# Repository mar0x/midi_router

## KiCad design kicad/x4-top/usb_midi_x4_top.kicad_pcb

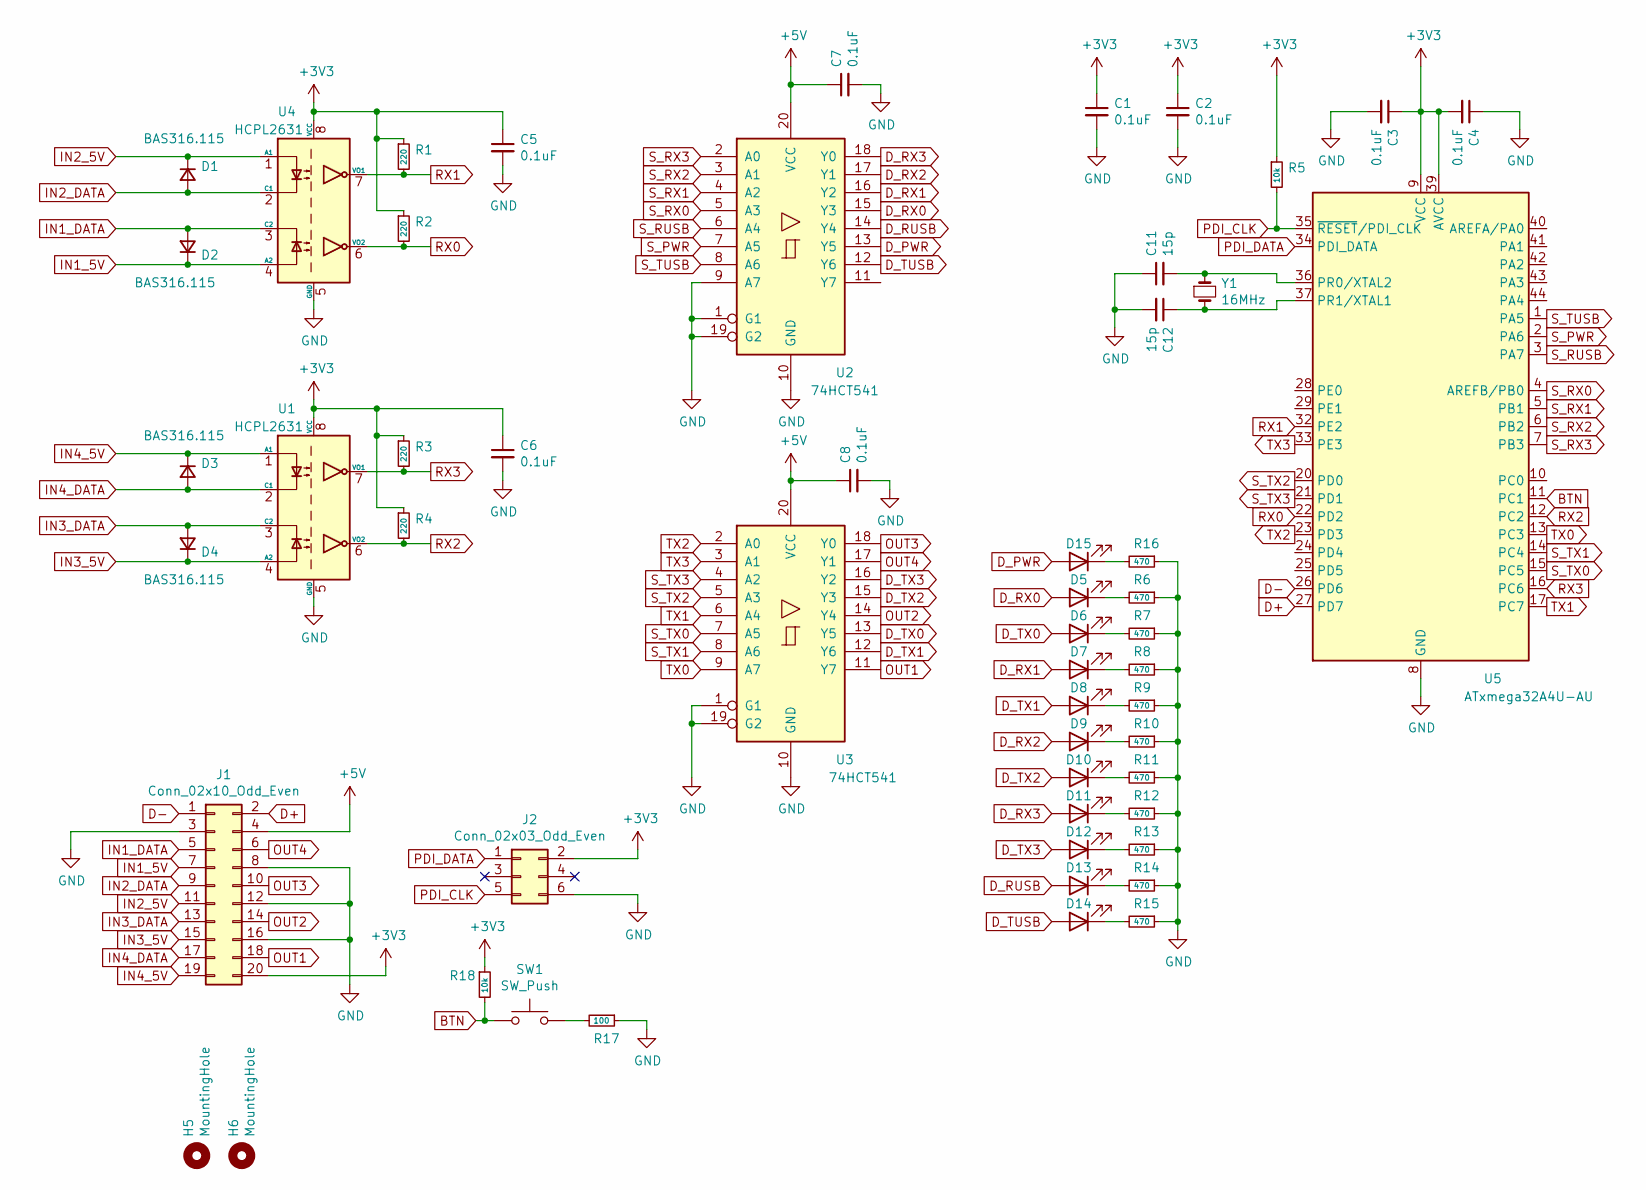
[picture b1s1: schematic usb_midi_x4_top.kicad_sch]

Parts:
C1, C2, C3, C4, C5, C6, C7, C8: 0.1uF; C_0805_2012Metric
C11, C12: 15p; C_0805_2012Metric
D1, D2, D3, D4: BAS316.115; D_SOD-323_HandSoldering
D5, D6, D7, D8, D9, D10, D11, D12, D13, D14, D15: LED; LED_D2.0mm_W4.8mm_Horizontal_O1.27mm_Z2.0mm
H5, H6: MountingHole; MountingHole_3.2mm_M3_Pad
J1: Conn_02x10_Odd_Even; PinSocket_2x10_P2.54mm_Vertical_SMD
J2: Conn_02x03_Odd_Even; IDC-Header_2x03_P2.54mm_Vertical
R1, R2, R3, R4: 220; R_0805_2012Metric
R5, R18: 10k; R_0805_2012Metric
R6, R7, R8, R9, R10, R11, R12, R13, R14, R15, R16: 470; R_0805_2012Metric
R17: 100; R_0805_2012Metric
SW1: SW_Push; SW_Tactile_SPST_Angled_PTS645Vx58-2LFS
U1, U4: HCPL2631; DIP-8_W7.62mm
U2, U3: 74HCT541; TSSOP-20_4.4x6.5mm_P0.65mm
U5: ATxmega32A4U-AU; TQFP-44_10x10mm_P0.8mm
Y1: 16MHz; Crystal_SMD_HC49-SD

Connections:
+3V3: C1.1, C2.1, C3.1, C4.2, C5.1, C6.1, J1.20, J2.2, R1.1, R2.1, R3.1, R4.1, R5.1, R18.1, U1.8 (VCC), U4.8 (VCC), U5.9 (VCC), U5.19 (VCC), U5.31 (VCC), U5.39 (AVCC)
+5V: C7.1, C8.1, J1.4, U2.20 (VCC), U3.20 (VCC)
BTN: R18.2, SW1.1, U5.11 (PC1)
D+: J1.2, U5.27 (PD7)
D-: J1.1, U5.26 (PD6)
D_PWR: D15.2 (A), U2.13 (Y5)
D_RUSB: D13.2 (A), U2.14 (Y4)
D_RX0: D5.2 (A), U2.15 (Y3)
D_RX1: D7.2 (A), U2.16 (Y2)
D_RX2: D9.2 (A), U2.17 (Y1)
D_RX3: D11.2 (A), U2.18 (Y0)
D_TUSB: D14.2 (A), U2.12 (Y6)
D_TX0: D6.2 (A), U3.13 (Y5)
D_TX1: D8.2 (A), U3.12 (Y6)
D_TX2: D10.2 (A), U3.15 (Y3)
D_TX3: D12.2 (A), U3.16 (Y2)
GND: C1.2, C2.2, C3.2, C4.1, C5.2, C6.2, C7.2, C8.2, C11.1, C12.2, J1.3, J1.8, J1.12, J1.16, J2.6, R6.1, R7.1, R8.1, R9.1, R10.1, R11.1, R12.1, R13.1, R14.1, R15.1, R16.1, R17.1, U1.5 (GND), U2.1 (G1), U2.9 (A7), U2.10 (GND), U2.19 (G2), U3.1 (G1), U3.10 (GND), U3.19 (G2), U4.5 (GND), U5.8 (GND), U5.18 (GND), U5.30 (GND), U5.38 (GND)
IN1_5V: D2.1 (K), J1.7, U4.4 (A2)
IN1_DATA: D2.2 (A), J1.5, U4.3 (C2)
IN2_5V: D1.1 (K), J1.11, U4.1 (A1)
IN2_DATA: D1.2 (A), J1.9, U4.2 (C1)
IN3_5V: D4.1 (K), J1.15, U1.4 (A2)
IN3_DATA: D4.2 (A), J1.13, U1.3 (C2)
IN4_5V: D3.1 (K), J1.19, U1.1 (A1)
IN4_DATA: D3.2 (A), J1.17, U1.2 (C1)
unnamed: C11.2, U5.36 (PR0/XTAL2), Y1.1
unnamed: C12.1, U5.37 (PR1/XTAL1), Y1.2
unnamed: D5.1 (K), R6.2
unnamed: D6.1 (K), R7.2
unnamed: D7.1 (K), R8.2
unnamed: D8.1 (K), R9.2
unnamed: D9.1 (K), R10.2
unnamed: D10.1 (K), R11.2
unnamed: D11.1 (K), R12.2
unnamed: D12.1 (K), R13.2
unnamed: D13.1 (K), R14.2
unnamed: D14.1 (K), R15.2
unnamed: D15.1 (K), R16.2
unnamed: R17.2, SW1.2
OUT1: J1.18, U3.11 (Y7)
OUT2: J1.14, U3.14 (Y4)
OUT3: J1.10, U3.18 (Y0)
OUT4: J1.6, U3.17 (Y1)
PDI_CLK: J2.5, R5.2, U5.35 (~RESET/PDI_CLK)
PDI_DATA: J2.1, U5.34 (PDI_DATA)
RX0: R2.2, U4.6 (VO2), U5.22 (PD2)
RX1: R1.2, U4.7 (VO1), U5.32 (PE2)
RX2: R4.2, U1.6 (VO2), U5.12 (PC2)
RX3: R3.2, U1.7 (VO1), U5.16 (PC6)
S_PWR: U2.7 (A5), U5.2 (PA6)
S_RUSB: U2.6 (A4), U5.3 (PA7)
S_RX0: U2.5 (A3), U5.4 (AREFB/PB0)
S_RX1: U2.4 (A2), U5.5 (PB1)
S_RX2: U2.3 (A1), U5.6 (PB2)
S_RX3: U2.2 (A0), U5.7 (PB3)
S_TUSB: U2.8 (A6), U5.1 (PA5)
S_TX0: U3.7 (A5), U5.15 (PC5)
S_TX1: U3.8 (A6), U5.14 (PC4)
S_TX2: U3.5 (A3), U5.20 (PD0)
S_TX3: U3.4 (A2), U5.21 (PD1)
TX0: U3.9 (A7), U5.13 (PC3)
TX1: U3.6 (A4), U5.17 (PC7)
TX2: U3.2 (A0), U5.23 (PD3)
TX3: U3.3 (A1), U5.33 (PE3)

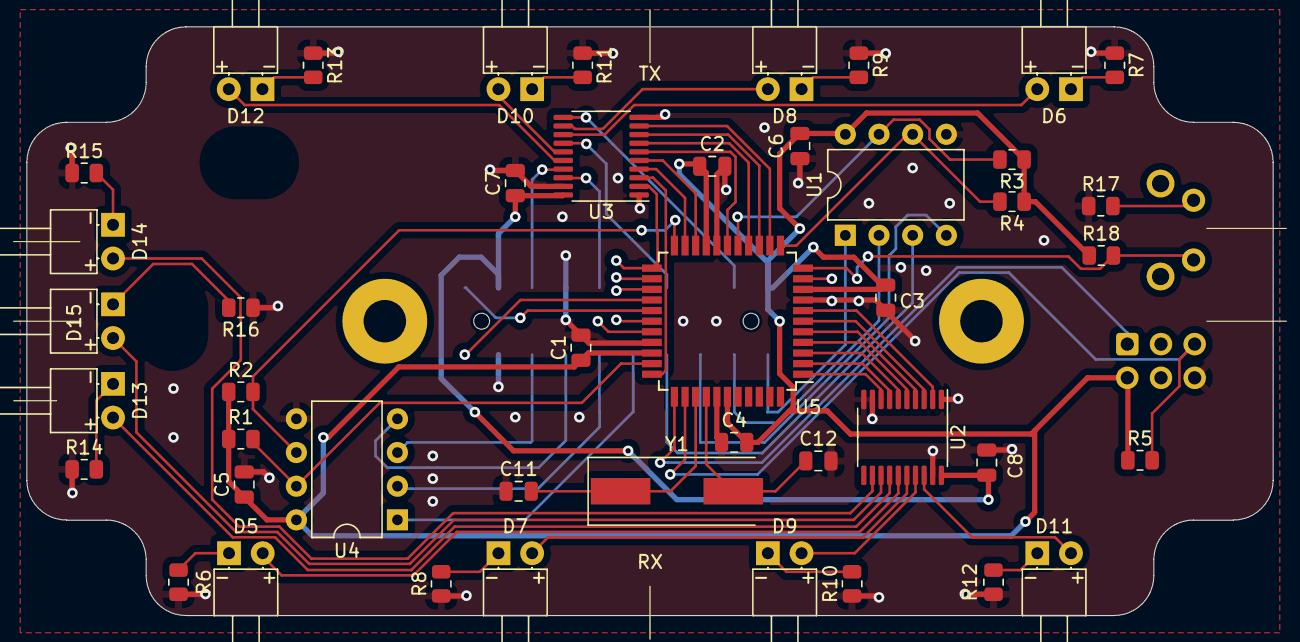
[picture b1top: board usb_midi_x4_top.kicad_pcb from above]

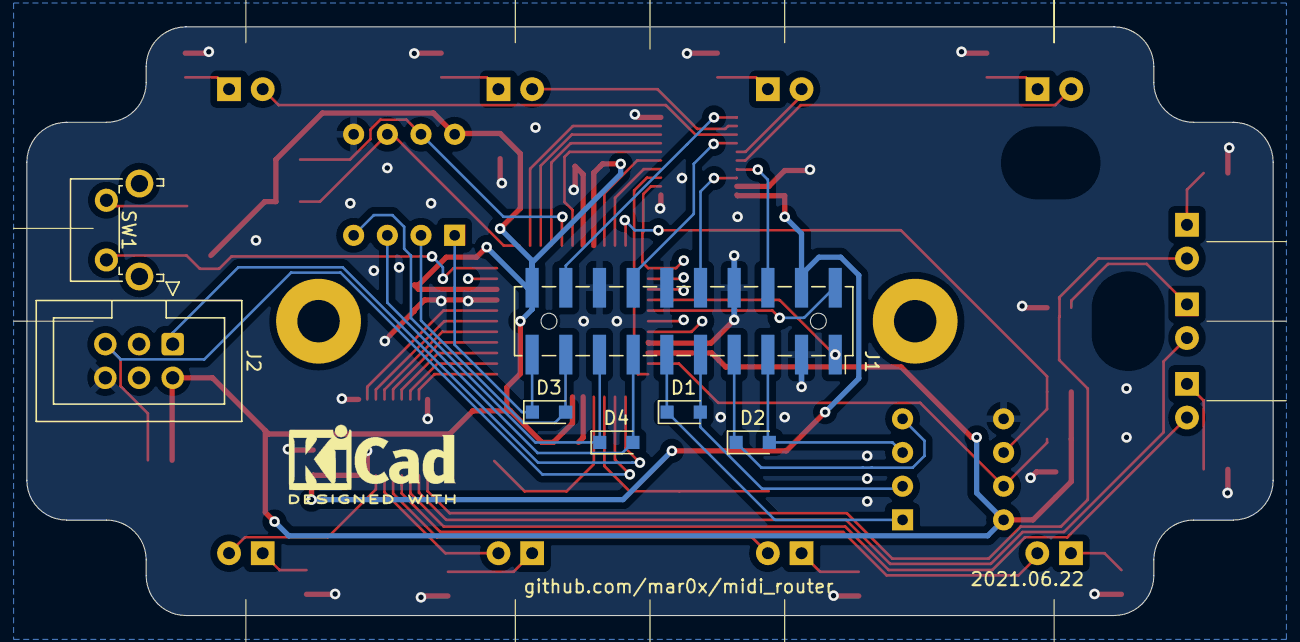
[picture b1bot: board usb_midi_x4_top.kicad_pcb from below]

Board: 2 copper layers, 94.0 x 44.4 mm, 54 parts (7 on the bottom side), 64 nets.

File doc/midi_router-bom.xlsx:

id | q | ref | desc | size | Vendor |  | Order info
 |  |  |  |  | URL | code | # | date | price | count | shipping | cost | cost per item
Top board
15 pF | 2 | C11 C12 | Кер.ЧИП конд. 15 пФ, C0G, 50В, 5% | 0805 | CC0805JRNPO9BN150 | #355297 | #07487681 | 06.07.2021 | 0.54 | 20 |  | 10.8 | 1.08
0.1 uF | 8 | C1 C2 C3 C4 C5 C6 C7 C8 | Кер.ЧИП конд. 0.1 мкФ, X7R, 50В, 10% | 0805 | CL21B104KBCNNNC | #817075 | #07487681 | 06.07.2021 | 0.47 | 100 |  | 47 | 3.76
BAS316 | 4 | D1 D2 D3 D4 | Диод импульсный | SOD-323 | BAS316 TP | #663682 | #07487681 | 06.07.2021 | 0.88 | 40 |  | 35.200000000000003 | 3.5200000000000005
L-13YD | 5 | D5 D7 D9 D11 D13 | Светодиод жёлтый |  | L-13YD | #307869 | #07487681 | 06.07.2021 | 5.4 | 50 |  | 270 | 27
L-13GD | 5 | D6 D8 D10 D12 D14 | Светодиод зелёный |  | L-13GD | #307956 | #07671493 | 08.11.2021 | 5 | 50 |  | 250 | 25
L-13ID | 1 | D15 | Светодиод красный |  | L-13ID | #307856 | #07487681 | 06.07.2021 | 5.0999999999999996 | 10 |  | 51 | 5.0999999999999996
 | 1 | J1 | PinSocket 2x5 |  |  | #33022627806 | #5010848944632510 | 12.06.2021 | 19.391999999999999 | 10 | 300.49 | 494.40999999999997 | 49.440999999999995
DS1013-06SSiB1-B-0 | 1 | J2 | IDC Header 2x3 |  | BH-06 | #9000058155 | #7174515 | 01.07.2021 | 10 | 10 |  | 100 | 10
470 | 15 | R1 R2 R3 R4 R6 R7 R8 R9 R10 R11 R12 R13 R14 R15 R16 | Резистор 470 Ом | 0805 | CR-05JL7--470R | #2782454 | #07487681 | 06.07.2021 | 0.12 | 150 |  | 18 | 1.7999999999999998
100 | 1 | R17 | Резистор 100 Ом | 0805
10 kOhm | 2 | R5 R18 | Резистор 10 кОм | 0805 | CR-05FL7---10K | #2782222 | #07655639 | 25.10.2021 | 0.14000000000000001 | 20 |  | 2.8 | 0.28000000000000003
 | 1 | SW1 | Кнопка |  | KLS7-TS6606-8.0-180 | #2177592 | #07655639 | 25.10.2021 | 2.2999999999999998 | 10 |  | 23 | 2.2999999999999998
74HCT541 | 2 | U2 U3 | Буферный элемент x8 | TSSOP-20 | MM74HCT541MTCX | #9000119229 | #7174515 | 01.07.2021 | 10.1 | 20 |  | 202 | 20.2
HCPL2730 | 0 | U1 U4 | Оптопара | DIP-8 | HCPL-2730 | #32906296742 | #5011970852262510 | 01.07.2021 | 17.940000000000001 | 40 | 190 | 907.6 | 0
HCPL2631 | 2 | U1 U4 | Оптопара | DIP-8 | HCPL-2631 |  | #5015224573612510 | 26.11.2021 | 8.2216666666666658 | 60 | 196.54 | 689.83999999999992 | 22.994666666666664
ATxmega32A4U-AU | 1 | U5 | Микроконтроллер | TQFP-44 |  | #4000592649273 | #5010170738742510 | 02.06.2021 | 149.11000000000001 | 5 | 317.52999999999997 | 1063.08 | 212.61599999999999
HC-49SD | 1 | Y1 | Кварцевый резонатор 16MHz |  | 12.881309999999999 | #219381 | #07487681 | 06.07.2021 | 11 | 10 |  | 110 | 11
Socket board
10 nF | 1 | C1 | Кер.ЧИП конд. 10 нФ, X7R, 100В, 10% | 0805 | CL21B103KCANNNC | #863513 | #07487681 | 06.07.2021 | 0.4 | 100 |  | 40 | 0.4
0.1 uF | 1 | C2 | Кер.ЧИП конд. 0.1 мкФ, X7R, 50В, 10% | 0805 | CL21B104KBCNNNC | #817075 | #07487681 | 06.07.2021 | 0.47 | 100 |  | 47 | 0.47
10 uF | 1 | C3 |  | 0805 | CL21A106KOQNNNG | #863492 | #07487681 | 06.07.2021 | 0.86 | 100 |  | 86 | 0.86
MF-MSMF050-2 | 1 | F1 | Fuse | 1812 | MF-MSMF050-2 | #186713 | #07487681 | 06.07.2021 | 3.2 | 10 |  | 32 | 3.2
 | 0.25 | J1 | PinHeader 2x5 |  | PLH-40 | #34079 | #7174515 | 01.07.2021 | 45 | 5 |  | 225 | 11.25
DS-5-01 | 8 | J2 J3 J4 J5 J6 J7 J10 J11 | MIDI разъём | DIN-5 | DS-5-01 | #1005002434565701 | #5009893661922510 | 18.04.2021 | 7.3760000000000003 | 100 | 775.44 | 1513.04 | 121.0432
USB-B | 1 | J8 | Разъём USB-B |  | DS1099-WN0-FE | #3638121 | #07487681 | 06.07.2021 | 6 | 10 |  | 60 | 6
220 Ohm | 12 | R2 R3 R4 R5 R7 R9 R10 R11 R12 R13 R22 R23 | Резистор 220 Ом | 0805 | CR-05JL7--220R | #2782412 | #07487681 | 06.07.2021 | 0.12 | 120 |  | 14.399999999999999 | 1.4399999999999997
USBLC6-2SC6 | 1 | U1 | Защита интерфейса USB | SOT-23-6 | USBLC6-2SC6 | #244787 | #07487681 | 06.07.2021 | 6.3 | 10 |  | 63 | 6.3
LD1117S33TR_SOT223 | 1 | U2 | Регулятор напряжения | SOT-223 | LD1117S33TR | #208059 | #07655639 | 25.10.2021 | 10.8 | 20 |  | 216 | 10.8
PCB | 1 |  |  |  |  |  |  |  | 75.724000000000004 | 10 | 729.22 | 1486.46 | 148.64600000000002
Box | 70 |  | Корпус, масса в граммах |  |  |  |  |  | 5.8666666666666663 | 750 |  | 4400 | 410.66666666666663
Стойки | 2 |  | Cтойки латунные 18мм | PCHSS-18 | PCHSS-18 |  | #5016317462462510 | 14.01.2022 | 15.9 | 20 |  | 318 | 31.8
Винт М3 | 4 |  | Винт М3x6мм | M3x6 | M3x6 A2 304 |  | #5016333550992510 | 14.01.2022 | 1.6434 | 100 |  | 164.34 | 6.5735999999999999
Саморез | 4 |  | Cаморез 2.6x12mm | 2.6x12 | 2.6x12mm Pan Head |  | #5012498625982510 | 03.08.2021 | 1.4508000000000001 | 100 |  | 145.08000000000001 | 5.8032000000000004
Шильдик | 1 |  |  |  |  |  |  |  | 10 | 1 |  | 10 | 10
Итого |  |  |  |  |  |  |  |  |  |  |  |  | 1171.3443333333332

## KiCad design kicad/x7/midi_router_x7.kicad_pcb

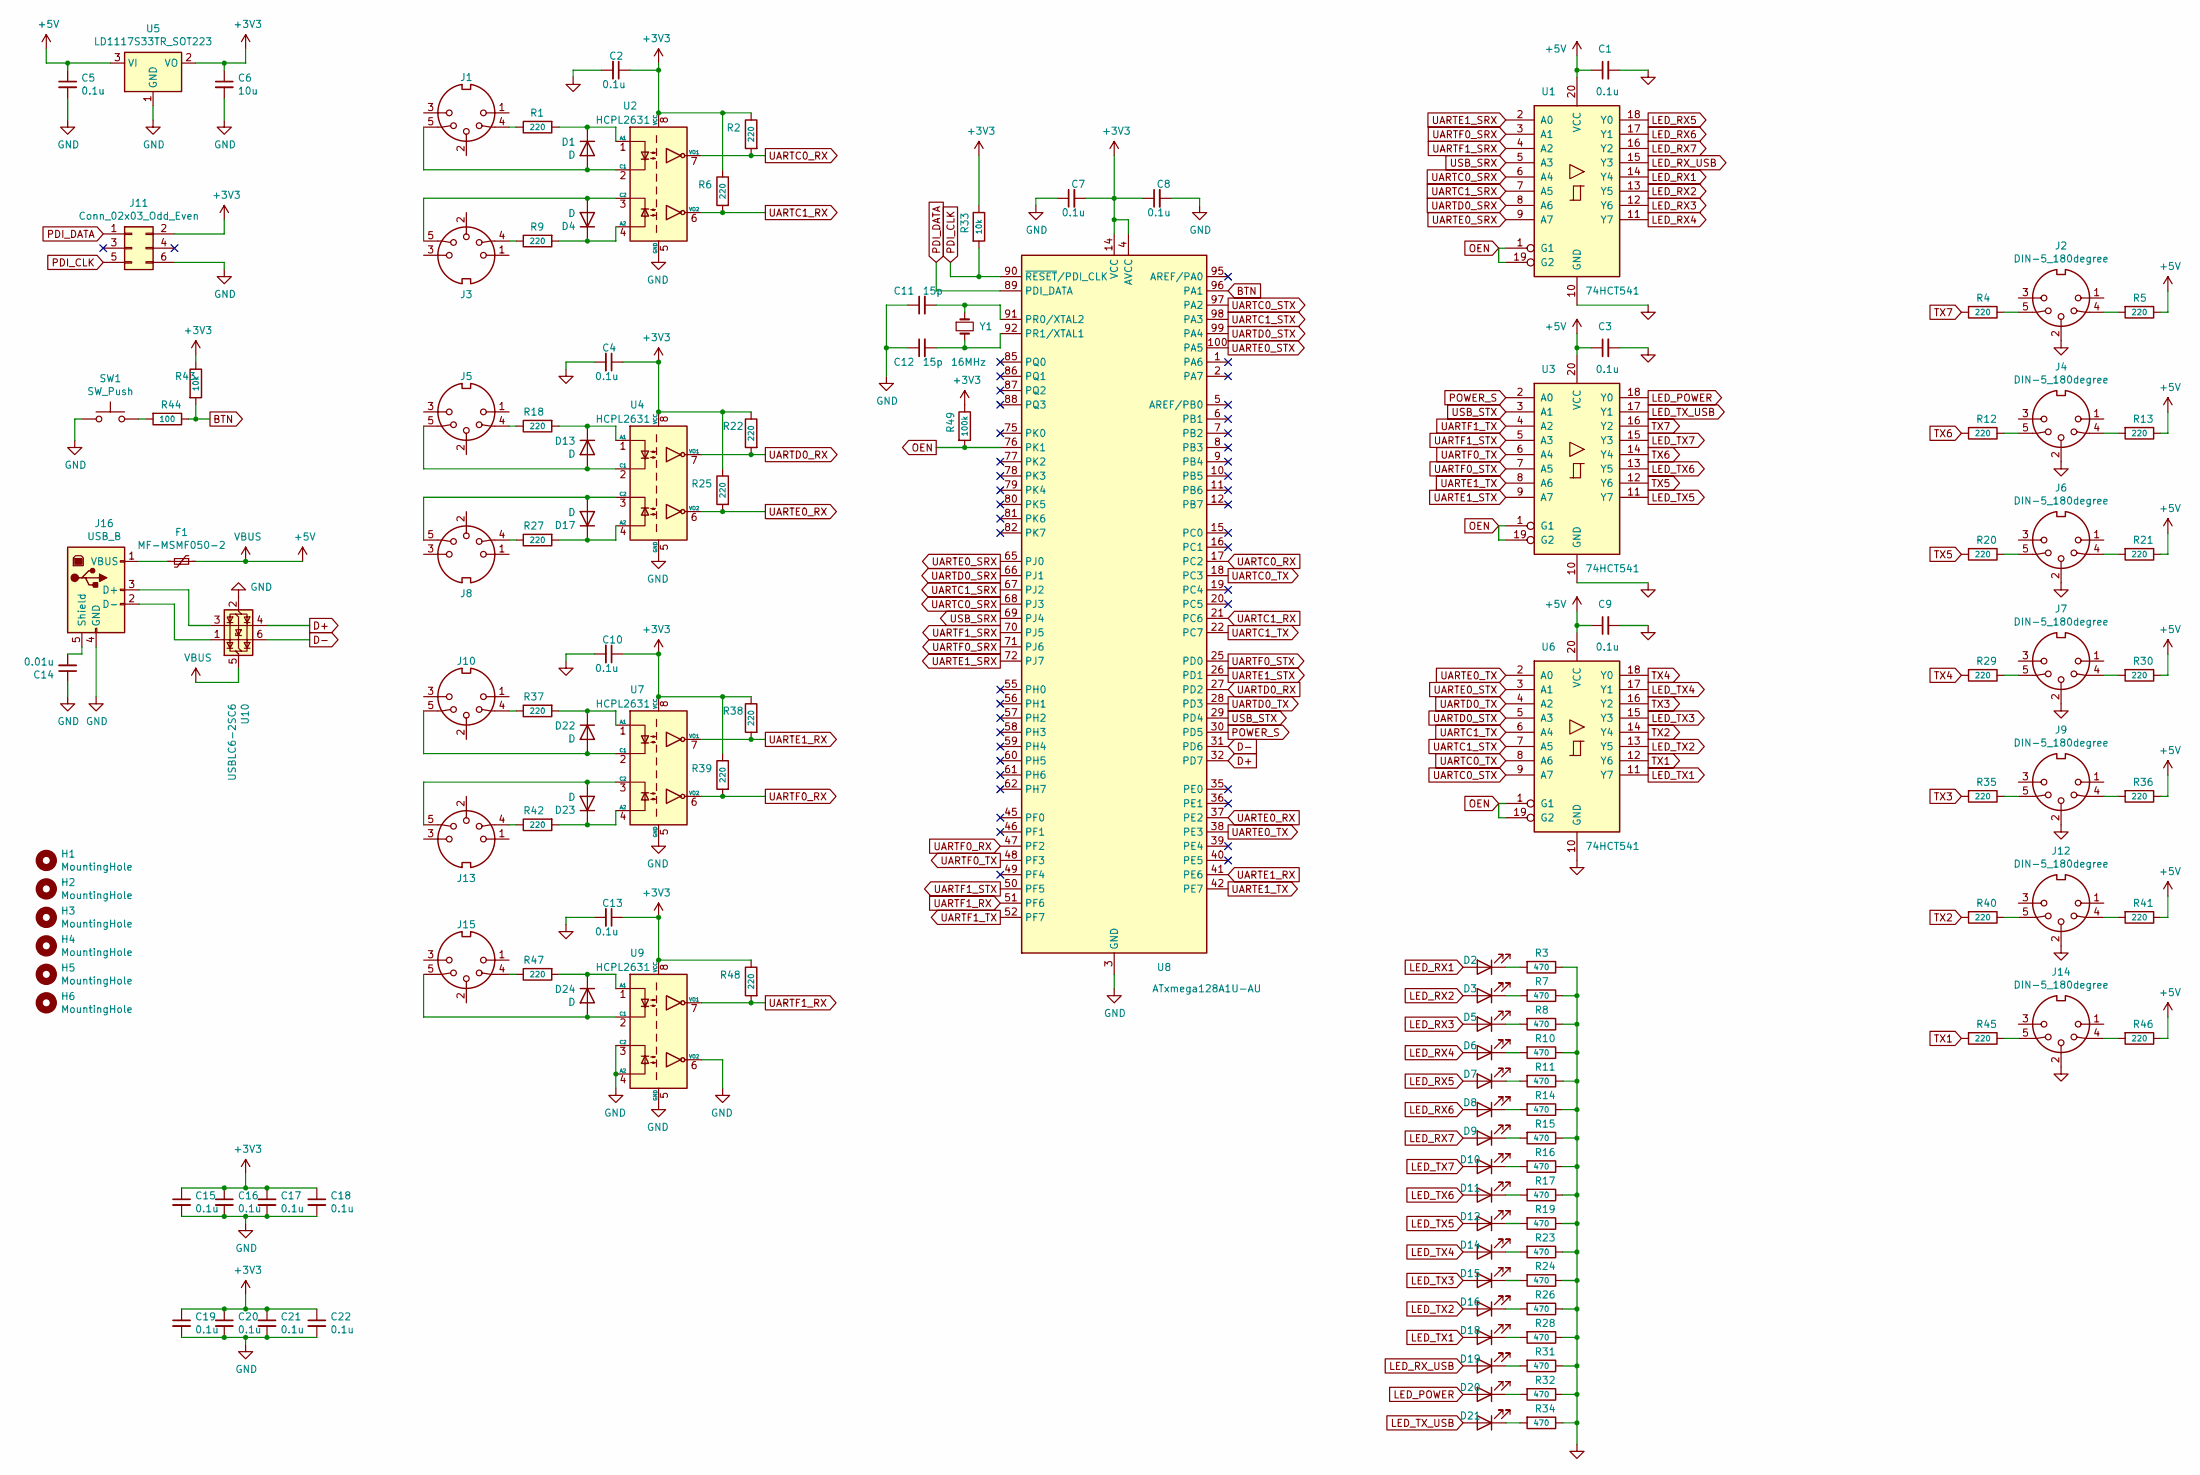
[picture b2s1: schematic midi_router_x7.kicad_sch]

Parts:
C1, C2, C3, C4, C5, C7, C8, C9, C10, C13, C15, C16, C17, C18, C19, C20, C21, C22: 0.1u; C_0805_2012Metric
C6: 10u; C_0805_2012Metric
C11, C12: 15p; C_0805_2012Metric
C14: 0.01u; C_0805_2012Metric
D1, D4, D13, D17, D22, D23, D24: D; D_SOD-323_HandSoldering
D2, D3, D5, D6, D7, D8, D9, D19: L-383YDT; PinSocket_1x02_P2.54mm_Vertical
D10, D11, D12, D14, D15, D16, D18, D21: L-383GDT; PinSocket_1x02_P2.54mm_Vertical
D20: L-383ID; PinSocket_1x02_P2.54mm_Vertical
F1: MF-MSMF050-2; Fuse_1812_4532Metric_Castellated
H1, H2, H3, H4, H5, H6: MountingHole; MountingHole_3.2mm_M3
J1, J2, J3, J4, J5, J6, J7, J8, J9, J10, J12, J13, J14, J15: DIN-5_180degree; DIN5MIDI-OOTDTY
J11: Conn_02x03_Odd_Even; IDC-Header_2x03_P2.54mm_Vertical
J16: USB_B; USB_B_OST_USB-B1HSxx_Horizontal
R1, R2, R4, R5, R6, R9, R12, R13, R18, R20, R21, R22, R25, R27, R29, R30, R35, R36, R37, R38, R39, R40, R41, R42, R45, R46, R47, R48: 220; R_0805_2012Metric
R3, R7, R8, R10, R11, R14, R15, R16, R17, R19, R23, R24, R26, R28, R31, R32, R34: 470; R_0805_2012Metric
R33, R43: 10k; R_0805_2012Metric
R44: 100; R_0805_2012Metric
R49: 100k; R_0805_2012Metric
SW1: SW_Push; SW_Tactile_SPST_Angled_PTS645Vx58-2LFS
U1, U3, U6: 74HCT541; TSSOP-20_4.4x6.5mm_P0.65mm
U2, U4, U7, U9: HCPL2631; DIP-8_W7.62mm
U5: LD1117S33TR_SOT223; SOT-223-3_TabPin2
U8: ATxmega128A1U-AU; TQFP-100_14x14mm_P0.5mm
U10: USBLC6-2SC6; SOT-23-6
Y1: 16MHz; Crystal_SMD_HC49-SD

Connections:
+3V3: C2.1, C4.1, C6.1, C7.2, C8.1, C10.1, C13.1, C15.1, C16.1, C17.1, C18.1, C19.1, C20.1, C21.1, C22.1, J11.2, R2.1, R6.1, R22.1, R25.1, R33.1, R38.1, R39.1, R43.1, R48.1, R49.1, U2.8 (VCC), U4.8 (VCC), U5.2 (VO), U7.8 (VCC), U8.4 (AVCC), U8.14 (VCC), U8.24 (VCC), U8.34 (VCC), U8.44 (VCC), U8.54 (VCC), U8.64 (VCC), U8.74 (VCC), U8.83 (VCC), U8.94 (AVCC), U9.8 (VCC)
+5V: C1.1, C3.1, C5.1, C9.1, F1.1, R5.1, R13.1, R21.1, R30.1, R36.1, R41.1, R46.1, U1.20 (VCC), U3.20 (VCC), U5.3 (VI), U6.20 (VCC), U10.5 (VBUS)
BTN: R43.2, R44.1, U8.96 (PA1)
D+: U8.32 (PD7), U10.4 (I/O2)
D-: U8.31 (PD6), U10.6 (I/O1)
GND: C1.2, C2.2, C3.2, C4.2, C5.2, C6.2, C7.1, C8.2, C9.2, C10.2, C11.1, C12.1, C13.2, C14.1, C15.2, C16.2, C17.2, C18.2, C19.2, C20.2, C21.2, C22.2, J2.2, J4.2, J6.2, J7.2, J9.2, J11.6, J12.2, J14.2, J16.4 (GND), R3.1, R7.1, R8.1, R10.1, R11.1, R14.1, R15.1, R16.1, R17.1, R19.1, R23.1, R24.1, R26.1, R28.1, R31.1, R32.1, R34.1, SW1.1, U1.10 (GND), U2.5 (GND), U3.10 (GND), U4.5 (GND), U5.1 (GND), U6.10 (GND), U7.5 (GND), U8.3 (GND), U8.13 (GND), U8.23 (GND), U8.33 (GND), U8.43 (GND), U8.53 (GND), U8.63 (GND), U8.73 (GND), U8.84 (GND), U8.93 (GND), U9.3 (C2), U9.4 (A2), U9.5 (GND), U9.6 (VO2), U10.2 (GND)
LED_POWER: D20.2 (A), U3.18 (Y0)
LED_RX1: D2.2 (A), U1.14 (Y4)
LED_RX2: D3.2 (A), U1.13 (Y5)
LED_RX3: D5.2 (A), U1.12 (Y6)
LED_RX4: D6.2 (A), U1.11 (Y7)
LED_RX5: D7.2 (A), U1.18 (Y0)
LED_RX6: D8.2 (A), U1.17 (Y1)
LED_RX7: D9.2 (A), U1.16 (Y2)
LED_RX_USB: D19.2 (A), U1.15 (Y3)
LED_TX1: D18.2 (A), U6.11 (Y7)
LED_TX2: D16.2 (A), U6.13 (Y5)
LED_TX3: D15.2 (A), U6.15 (Y3)
LED_TX4: D14.2 (A), U6.17 (Y1)
LED_TX5: D12.2 (A), U3.11 (Y7)
LED_TX6: D11.2 (A), U3.13 (Y5)
LED_TX7: D10.2 (A), U3.15 (Y3)
LED_TX_USB: D21.2 (A), U3.17 (Y1)
unnamed: C11.2, U8.91 (PR0/XTAL2), Y1.1
unnamed: C12.2, U8.92 (PR1/XTAL1), Y1.2
unnamed: C14.2, J16.5 (Shield)
unnamed: D1.1 (K), R1.2, U2.1 (A1)
unnamed: D1.2 (A), J1.5, U2.2 (C1)
unnamed: D2.1 (K), R3.2
unnamed: D3.1 (K), R7.2
unnamed: D4.1 (K), R9.2, U2.4 (A2)
unnamed: D4.2 (A), J3.5, U2.3 (C2)
unnamed: D5.1 (K), R8.2
unnamed: D6.1 (K), R10.2
unnamed: D7.1 (K), R11.2
unnamed: D8.1 (K), R14.2
unnamed: D9.1 (K), R15.2
unnamed: D10.1 (K), R16.2
unnamed: D11.1 (K), R17.2
unnamed: D12.1 (K), R19.2
unnamed: D13.1 (K), R18.2, U4.1 (A1)
unnamed: D13.2 (A), J5.5, U4.2 (C1)
unnamed: D14.1 (K), R23.2
unnamed: D15.1 (K), R24.2
unnamed: D16.1 (K), R26.2
unnamed: D17.1 (K), R27.2, U4.4 (A2)
unnamed: D17.2 (A), J8.5, U4.3 (C2)
unnamed: D18.1 (K), R28.2
unnamed: D19.1 (K), R31.2
unnamed: D20.1 (K), R32.2
unnamed: D21.1 (K), R34.2
unnamed: D22.1 (K), R37.2, U7.1 (A1)
unnamed: D22.2 (A), J10.5, U7.2 (C1)
unnamed: D23.1 (K), R42.2, U7.4 (A2)
unnamed: D23.2 (A), J13.5, U7.3 (C2)
unnamed: D24.1 (K), R47.2, U9.1 (A1)
unnamed: D24.2 (A), J15.5, U9.2 (C1)
unnamed: F1.2, J16.1 (VBUS)
unnamed: J1.4, R1.1
unnamed: J2.4, R5.2
unnamed: J2.5, R4.1
unnamed: J3.4, R9.1
unnamed: J4.4, R13.2
unnamed: J4.5, R12.1
unnamed: J5.4, R18.1
unnamed: J6.4, R21.2
unnamed: J6.5, R20.1
unnamed: J7.4, R30.2
unnamed: J7.5, R29.1
unnamed: J8.4, R27.1
unnamed: J9.4, R36.2
unnamed: J9.5, R35.1
unnamed: J10.4, R37.1
unnamed: J12.4, R41.2
unnamed: J12.5, R40.1
unnamed: J13.4, R42.1
unnamed: J14.4, R46.2
unnamed: J14.5, R45.1
unnamed: J15.4, R47.1
unnamed: J16.2 (D-), U10.1 (I/O1)
unnamed: J16.3 (D+), U10.3 (I/O2)
unnamed: R44.2, SW1.2
OEN: R49.2, U1.1 (G1), U1.19 (G2), U3.1 (G1), U3.19 (G2), U6.1 (G1), U6.19 (G2), U8.76 (PK1)
PDI_CLK: J11.5, R33.2, U8.90 (~RESET/PDI_CLK)
PDI_DATA: J11.1, U8.89 (PDI_DATA)
POWER_S: U3.2 (A0), U8.30 (PD5)
TX1: R45.2, U6.12 (Y6)
TX2: R40.2, U6.14 (Y4)
TX3: R35.2, U6.16 (Y2)
TX4: R29.2, U6.18 (Y0)
TX5: R20.2, U3.12 (Y6)
TX6: R12.2, U3.14 (Y4)
TX7: R4.2, U3.16 (Y2)
UARTC0_RX: R2.2, U2.7 (VO1), U8.17 (PC2)
UARTC0_SRX: U1.6 (A4), U8.68 (PJ3)
UARTC0_STX: U6.9 (A7), U8.97 (PA2)
UARTC0_TX: U6.8 (A6), U8.18 (PC3)
UARTC1_RX: R6.2, U2.6 (VO2), U8.21 (PC6)
UARTC1_SRX: U1.7 (A5), U8.67 (PJ2)
UARTC1_STX: U6.7 (A5), U8.98 (PA3)
UARTC1_TX: U6.6 (A4), U8.22 (PC7)
UARTD0_RX: R22.2, U4.7 (VO1), U8.27 (PD2)
UARTD0_SRX: U1.8 (A6), U8.66 (PJ1)
UARTD0_STX: U6.5 (A3), U8.99 (PA4)
UARTD0_TX: U6.4 (A2), U8.28 (PD3)
UARTE0_RX: R25.2, U4.6 (VO2), U8.37 (PE2)
UARTE0_SRX: U1.9 (A7), U8.65 (PJ0)
UARTE0_STX: U6.3 (A1), U8.100 (PA5)
UARTE0_TX: U6.2 (A0), U8.38 (PE3)
UARTE1_RX: R38.2, U7.7 (VO1), U8.41 (PE6)
UARTE1_SRX: U1.2 (A0), U8.72 (PJ7)
UARTE1_STX: U3.9 (A7), U8.26 (PD1)
UARTE1_TX: U3.8 (A6), U8.42 (PE7)
UARTF0_RX: R39.2, U7.6 (VO2), U8.47 (PF2)
UARTF0_SRX: U1.3 (A1), U8.71 (PJ6)
UARTF0_STX: U3.7 (A5), U8.25 (PD0)
UARTF0_TX: U3.6 (A4), U8.48 (PF3)
UARTF1_RX: R48.2, U8.51 (PF6), U9.7 (VO1)
UARTF1_SRX: U1.4 (A2), U8.70 (PJ5)
UARTF1_STX: U3.5 (A3), U8.50 (PF5)
UARTF1_TX: U3.4 (A2), U8.52 (PF7)
USB_SRX: U1.5 (A3), U8.69 (PJ4)
USB_STX: U3.3 (A1), U8.29 (PD4)

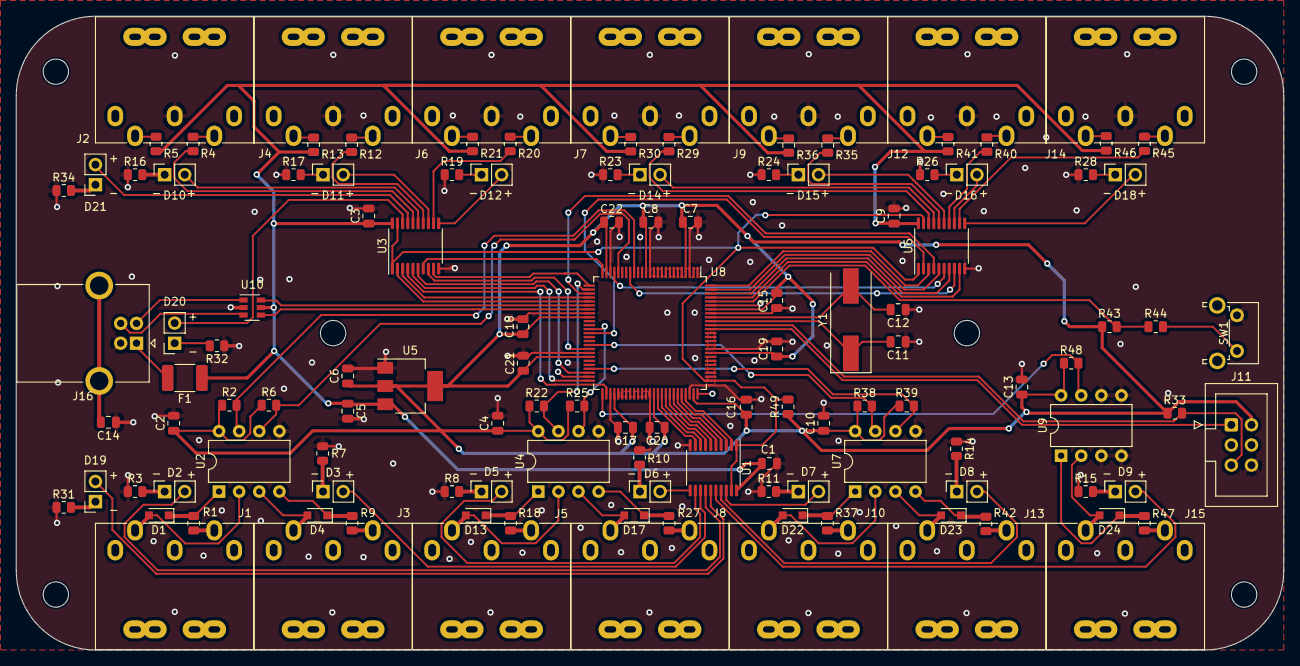
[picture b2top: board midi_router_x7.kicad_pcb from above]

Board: 2 copper layers, 160.0 x 80.0 mm, 130 parts (0 on the bottom side), 123 nets.

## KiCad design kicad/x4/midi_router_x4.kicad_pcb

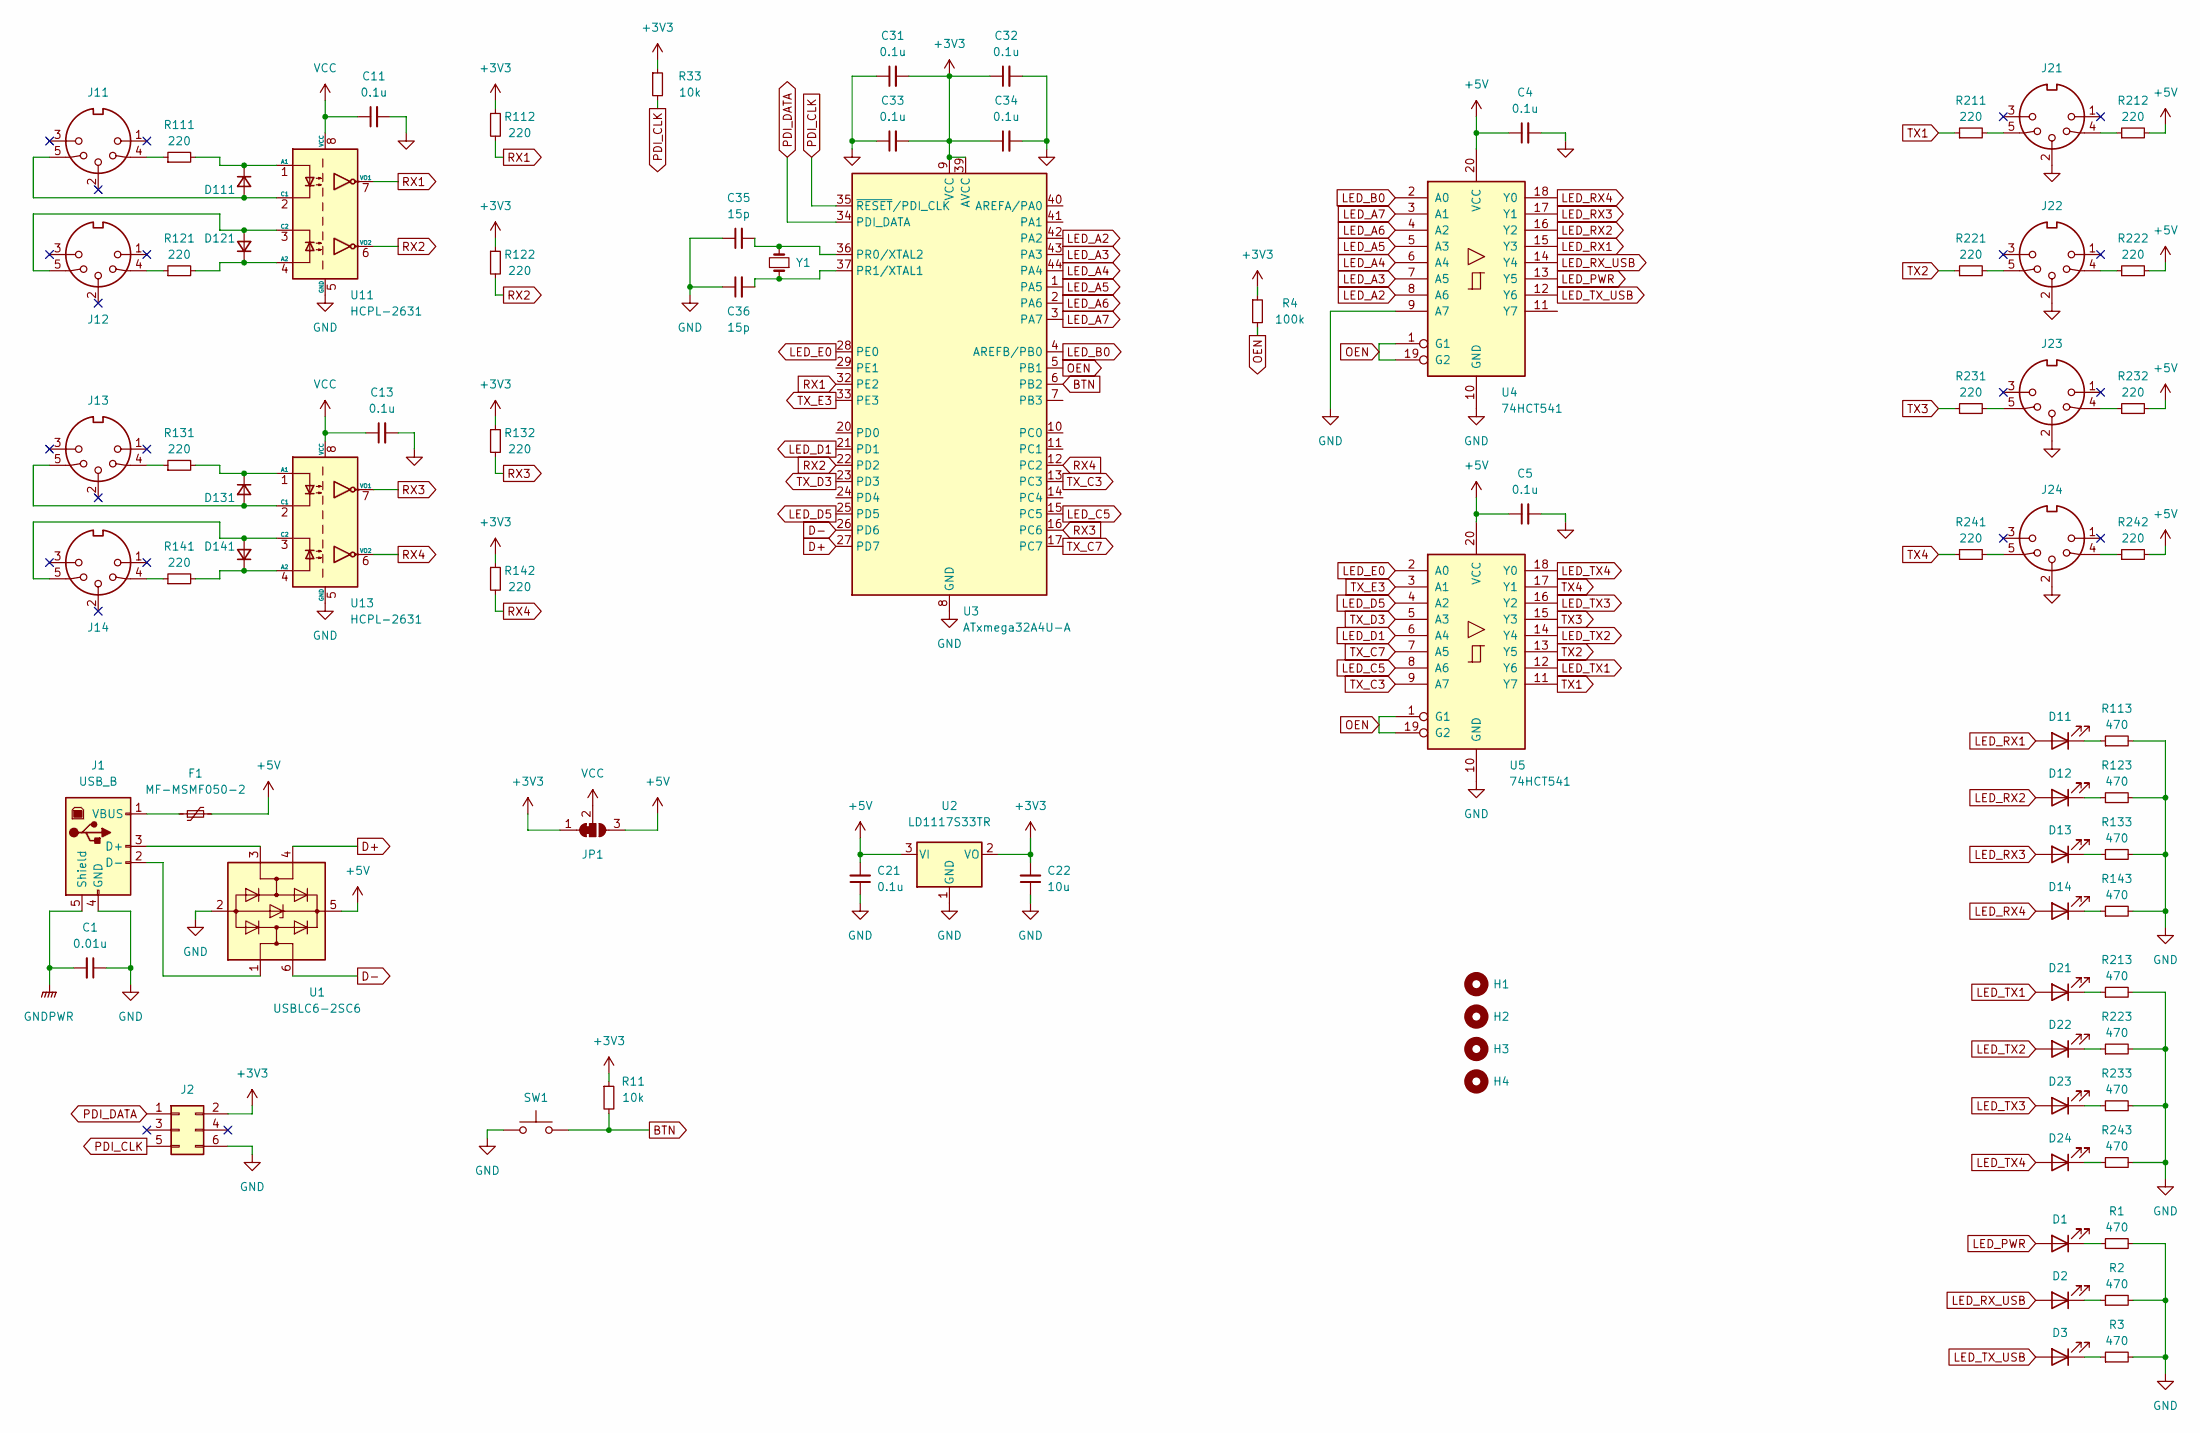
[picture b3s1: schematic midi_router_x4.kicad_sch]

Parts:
C1: 0.01u; C_0805_2012Metric_Pad1.18x1.45mm_HandSolder
C4, C5, C11, C13, C21, C31, C32, C33, C34: 0.1u; C_0805_2012Metric_Pad1.18x1.45mm_HandSolder
C22: 10u; C_0805_2012Metric_Pad1.18x1.45mm_HandSolder
C35, C36: 15p; C_0805_2012Metric_Pad1.18x1.45mm_HandSolder
D1, D2, D3, D11, D12, D13, D14, D21, D22, D23, D24: LED; PinSocket_1x02_P2.54mm_Vertical
D111, D121, D131, D141: D_Small; D_SOD-323_HandSoldering
F1: MF-MSMF050-2; Fuse_1812_4532Metric_Pad1.30x3.40mm_HandSolder
H1, H2, H3, H4: MountingHole; MountingHole_3.2mm_M3_DIN965
J1: USB_B; USB_B_OST_USB-B1HSxx_Horizontal
J2: Conn_02x03_Odd_Even; IDC-Header_2x03_P2.54mm_Vertical
J11, J12, J13, J14, J21, J22, J23, J24: DIN-5_180degree; DIN5MIDI-OOTDTY
JP1: SolderJumper_3_Bridged12; SolderJumper-3_P1.3mm_Bridged2Bar12_Pad1.0x1.5mm
R1, R2, R3, R113, R123, R133, R143, R213, R223, R233, R243: 470; R_0805_2012Metric_Pad1.20x1.40mm_HandSolder
R4: 100k; R_0805_2012Metric_Pad1.20x1.40mm_HandSolder
R11, R33: 10k; R_0805_2012Metric_Pad1.20x1.40mm_HandSolder
R111, R112, R121, R122, R131, R132, R141, R142, R211, R212, R221, R222, R231, R232, R241, R242: 220; R_0805_2012Metric_Pad1.20x1.40mm_HandSolder
SW1: SW_Push; SW_Tactile_SPST_Angled_PTS645Vx58-2LFS
U1: USBLC6-2SC6; SOT-23-6_Handsoldering
U2: LD1117S33TR; SOT-223-3_TabPin2
U3: ATxmega32A4U-A; TQFP-44_10x10mm_P0.8mm
U4, U5: 74HCT541; TSSOP-20_4.4x6.5mm_P0.65mm
U11, U13: HCPL-2631; DIP-8_W7.62mm
Y1: Crystal_Small; Crystal_SMD_HC49-SD

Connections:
+3V3: C22.2, C31.2, C32.1, C33.2, C34.1, J2.2, JP1.1 (A), R4.1, R11.1, R33.1, R112.1, R122.1, R132.1, R142.1, U2.2 (VO), U3.9 (VCC), U3.19 (VCC), U3.31 (VCC), U3.39 (AVCC)
+5V: C4.1, C5.1, C21.2, F1.2, JP1.3 (B), R212.2, R222.2, R232.2, R242.2, U1.5 (VBUS), U2.3 (VI), U4.20 (VCC), U5.20 (VCC)
BTN: R11.2, SW1.2, U3.6 (PB2)
D+: U1.4 (I/O2), U3.27 (PD7)
D-: U1.6 (I/O1), U3.26 (PD6)
GND: C1.1, C4.2, C5.2, C11.2, C13.2, C21.1, C22.1, C31.1, C32.2, C33.1, C34.2, C35.1, C36.1, J1.4 (GND), J2.6, J21.2, J22.2, J23.2, J24.2, R1.2, R2.2, R3.2, R113.2, R123.2, R133.2, R143.2, R213.2, R223.2, R233.2, R243.2, SW1.1, U1.2 (GND), U2.1 (GND), U3.8 (GND), U3.18 (GND), U3.30 (GND), U3.38 (GND), U4.9 (A7), U4.10 (GND), U5.10 (GND), U11.5 (GND), U13.5 (GND)
GNDPWR: C1.2, J1.5 (Shield)
LED_A2: U3.42 (PA2), U4.8 (A6)
LED_A3: U3.43 (PA3), U4.7 (A5)
LED_A4: U3.44 (PA4), U4.6 (A4)
LED_A5: U3.1 (PA5), U4.5 (A3)
LED_A6: U3.2 (PA6), U4.4 (A2)
LED_A7: U3.3 (PA7), U4.3 (A1)
LED_B0: U3.4 (AREFB/PB0), U4.2 (A0)
LED_C5: U3.15 (PC5), U5.8 (A6)
LED_D1: U3.21 (PD1), U5.6 (A4)
LED_D5: U3.25 (PD5), U5.4 (A2)
LED_E0: U3.28 (PE0), U5.2 (A0)
LED_PWR: D1.2 (A), U4.13 (Y5)
LED_RX1: D11.2 (A), U4.15 (Y3)
LED_RX2: D12.2 (A), U4.16 (Y2)
LED_RX3: D13.2 (A), U4.17 (Y1)
LED_RX4: D14.2 (A), U4.18 (Y0)
LED_RX_USB: D2.2 (A), U4.14 (Y4)
LED_TX1: D21.2 (A), U5.12 (Y6)
LED_TX2: D22.2 (A), U5.14 (Y4)
LED_TX3: D23.2 (A), U5.16 (Y2)
LED_TX4: D24.2 (A), U5.18 (Y0)
LED_TX_USB: D3.2 (A), U4.12 (Y6)
unnamed: C35.2, U3.36 (PR0/XTAL2), Y1.2
unnamed: C36.2, U3.37 (PR1/XTAL1), Y1.1
unnamed: D1.1 (K), R1.1
unnamed: D2.1 (K), R2.1
unnamed: D3.1 (K), R3.1
unnamed: D11.1 (K), R113.1
unnamed: D12.1 (K), R123.1
unnamed: D13.1 (K), R133.1
unnamed: D14.1 (K), R143.1
unnamed: D21.1 (K), R213.1
unnamed: D22.1 (K), R223.1
unnamed: D23.1 (K), R233.1
unnamed: D24.1 (K), R243.1
unnamed: D111.1 (K), R111.2, U11.1 (A1)
unnamed: D111.2 (A), J11.5, U11.2 (C1)
unnamed: D121.1 (K), R121.2, U11.4 (A2)
unnamed: D121.2 (A), J12.5, U11.3 (C2)
unnamed: D131.1 (K), R131.2, U13.1 (A1)
unnamed: D131.2 (A), J13.5, U13.2 (C1)
unnamed: D141.1 (K), R141.2, U13.4 (A2)
unnamed: D141.2 (A), J14.5, U13.3 (C2)
unnamed: F1.1, J1.1 (VBUS)
unnamed: J1.2 (D-), U1.1 (I/O1)
unnamed: J1.3 (D+), U1.3 (I/O2)
unnamed: J11.4, R111.1
unnamed: J12.4, R121.1
unnamed: J13.4, R131.1
unnamed: J14.4, R141.1
unnamed: J21.4, R212.1
unnamed: J21.5, R211.2
unnamed: J22.4, R222.1
unnamed: J22.5, R221.2
unnamed: J23.4, R232.1
unnamed: J23.5, R231.2
unnamed: J24.4, R242.1
unnamed: J24.5, R241.2
OEN: R4.2, U3.5 (PB1), U4.1 (G1), U4.19 (G2), U5.1 (G1), U5.19 (G2)
PDI_CLK: J2.5, R33.2, U3.35 (~RESET/PDI_CLK)
PDI_DATA: J2.1, U3.34 (PDI_DATA)
RX1: R112.2, U3.32 (PE2), U11.7 (VO1)
RX2: R122.2, U3.22 (PD2), U11.6 (VO2)
RX3: R132.2, U3.16 (PC6), U13.7 (VO1)
RX4: R142.2, U3.12 (PC2), U13.6 (VO2)
TX1: R211.1, U5.11 (Y7)
TX2: R221.1, U5.13 (Y5)
TX3: R231.1, U5.15 (Y3)
TX4: R241.1, U5.17 (Y1)
TX_C3: U3.13 (PC3), U5.9 (A7)
TX_C7: U3.17 (PC7), U5.7 (A5)
TX_D3: U3.23 (PD3), U5.5 (A3)
TX_E3: U3.33 (PE3), U5.3 (A1)
VCC: C11.1, C13.1, JP1.2 (C), U11.8 (VCC), U13.8 (VCC)
